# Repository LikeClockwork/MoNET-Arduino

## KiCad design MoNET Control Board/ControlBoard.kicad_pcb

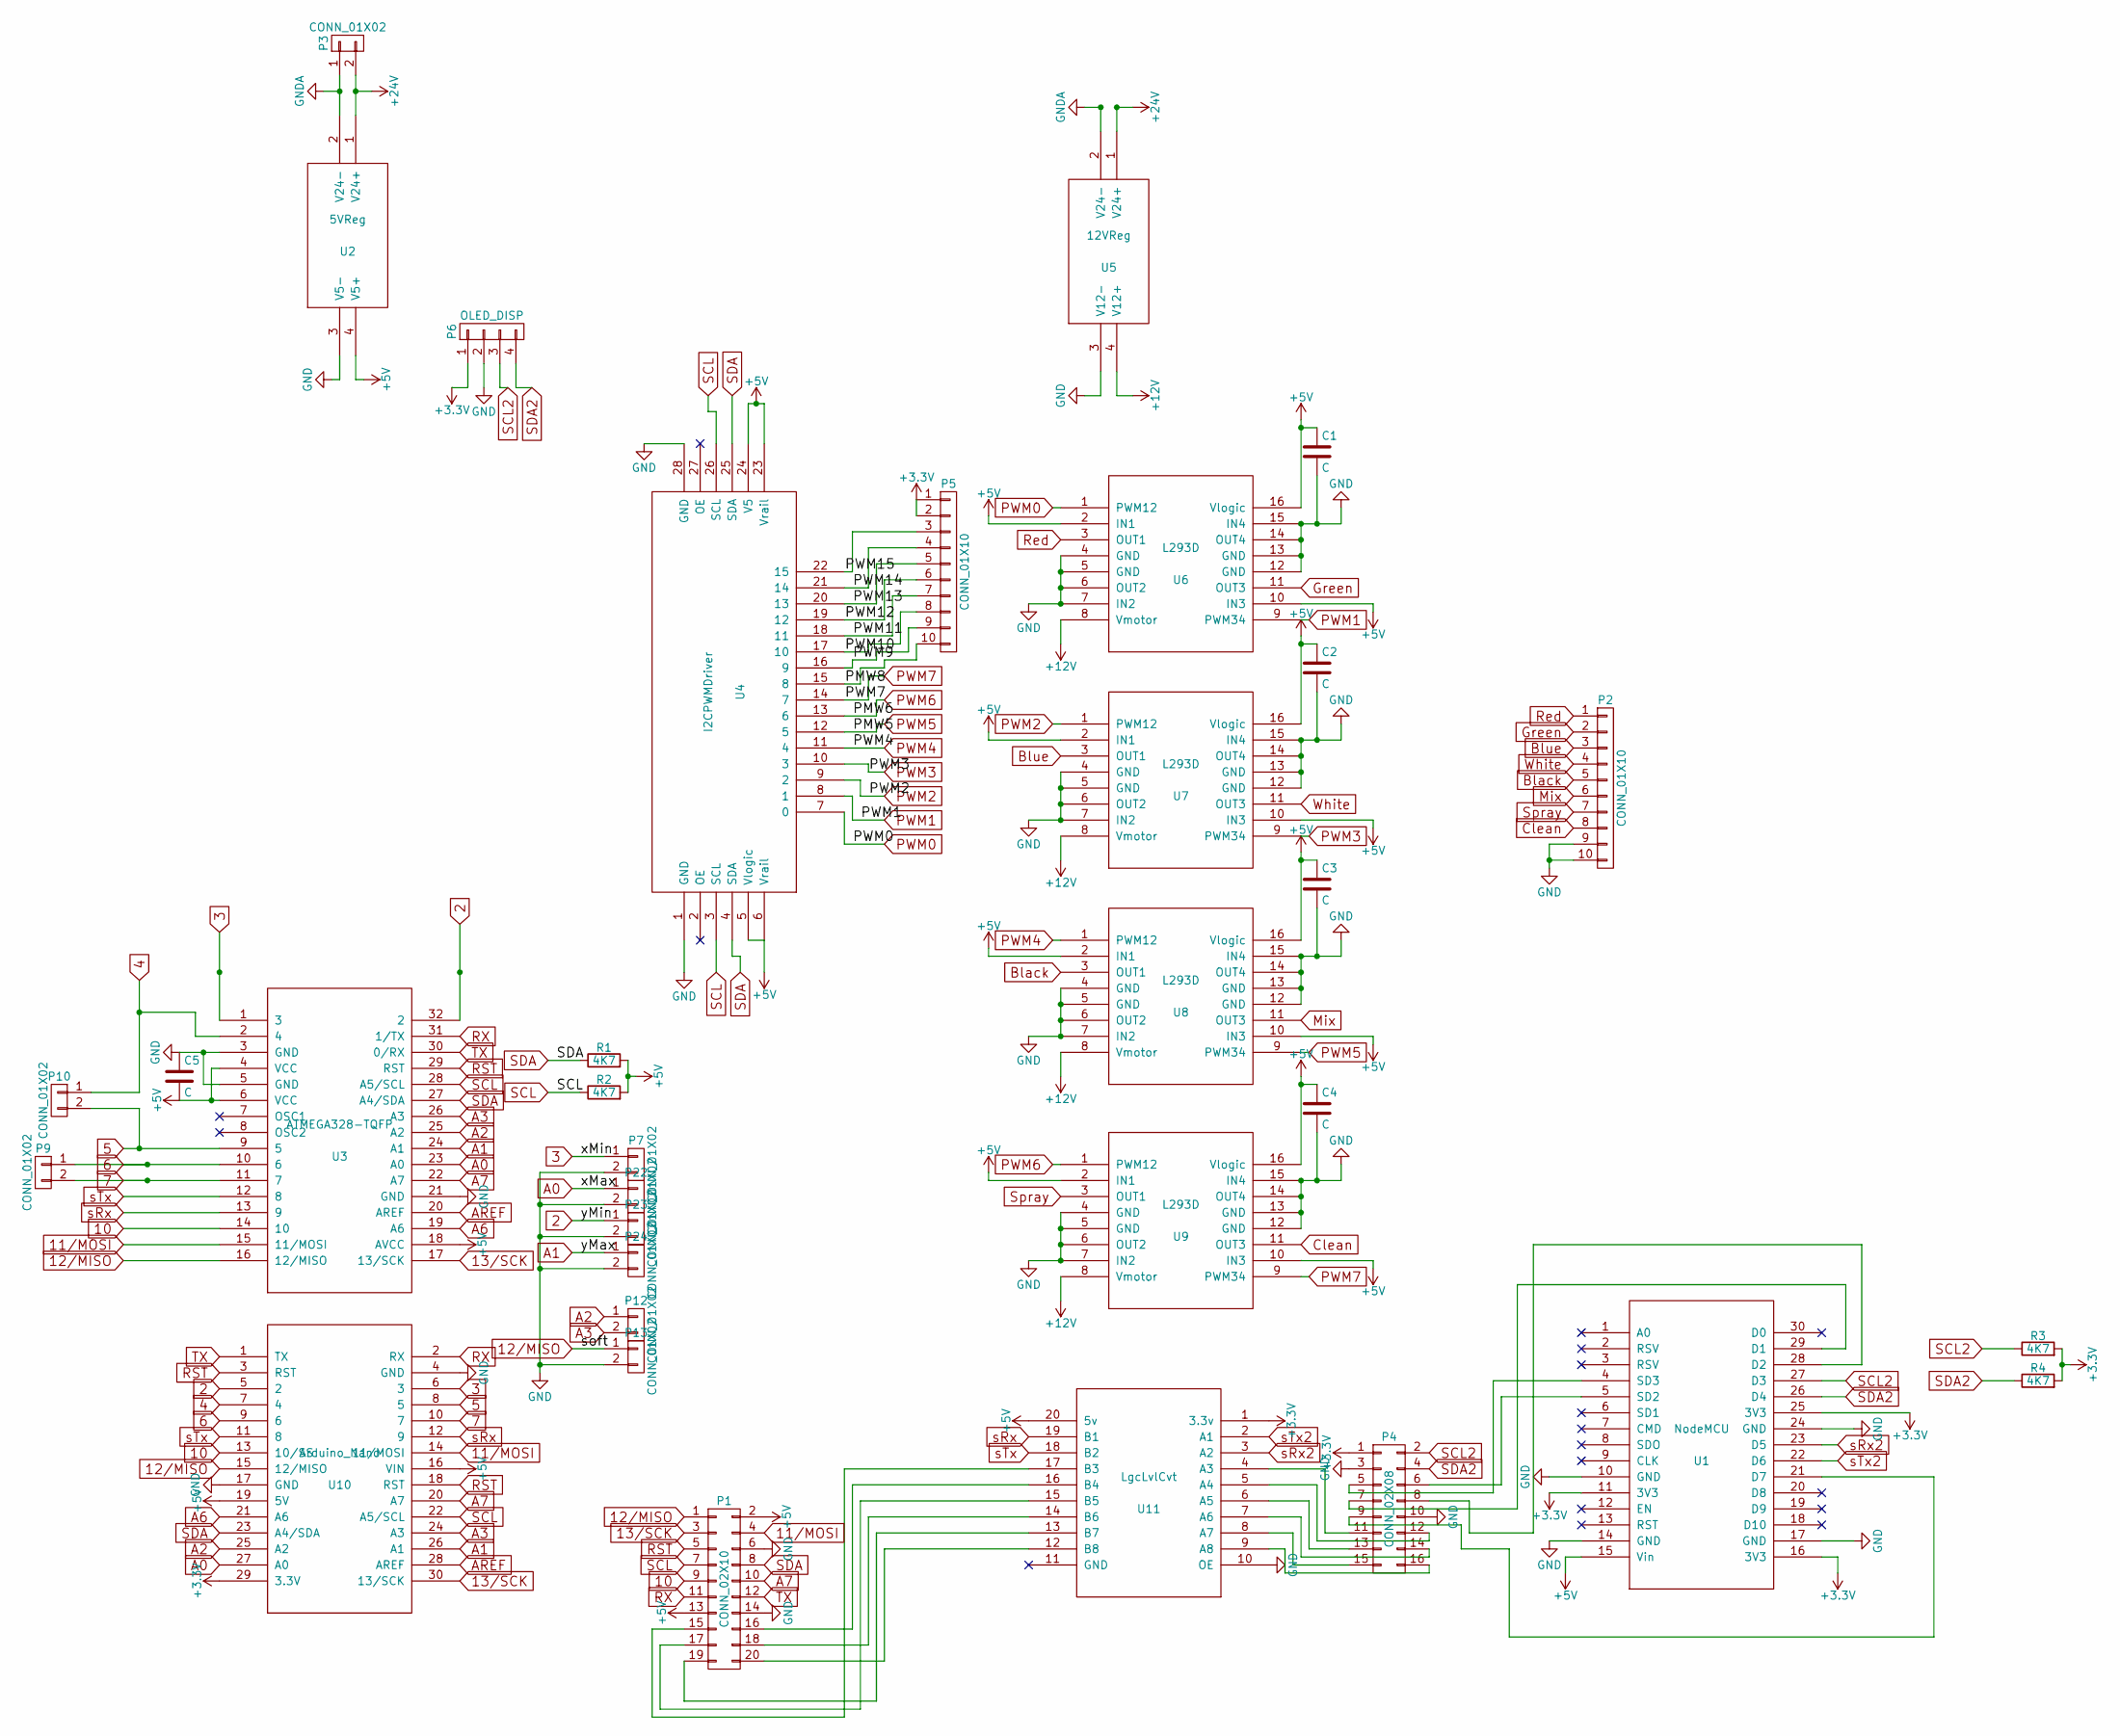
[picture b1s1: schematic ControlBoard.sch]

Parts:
C1, C2, C3, C4, C5: C; C_0603_HandSoldering
P1: CONN_02X10; Pin_Header_Straight_2x10
P2: CONN_01X10; SCREWTERM_01X10
P3, P7, P9, P10, P12, P13, P22, P23, P24: CONN_01X02; SCREWTERM_01X02
P4: CONN_02X08; Pin_Header_Straight_2x08
P5: CONN_01X10; Pin_Header_Straight_2x05
P6: OLED_DISP; Pin_Header_Straight_1x04
R1, R2, R3, R4: 4K7; R_0603_HandSoldering
U1: NodeMCU; NODEMCU
U2: 5VReg; RioRandVoltReg
U3: ATMEGA328-TQFP; TQFP32-08
U4: I2CPWMDriver; I2C_PWM_DRIVER
U5: 12VReg; RioRandVoltReg
U6, U7, U8, U9: L293D
U10: Arduino_Nano
U11: LgcLvlCvt

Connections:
2: P23.1, U3.32 (2), U10.5 (2)
3: P7.1, U3.1 (3), U10.6 (3)
4: P10.1, U3.2 (4), U10.7 (4)
5: P10.2, U3.9 (5), U10.8 (5)
6: P9.1, U3.10 (6), U10.9 (6)
7: P9.2, U3.11 (7), U10.10 (7)
10: P1.9, U3.14 (10), U10.13 (10/SS)
11/MOSI: P1.4, U3.15 (11/MOSI), U10.14 (11/MOSI)
12/MISO: P1.1, P13.1, U3.16 (12/MISO), U10.15 (12/MISO)
13/SCK: P1.3, U3.17 (13/SCK), U10.30 (13/SCK)
+3V3: P4.1, P5.1, P5.2, P6.1, R3.2, R4.2, U1.11 (3V3), U1.16 (3V3), U1.25 (3V3), U10.29 (3.3V), U11.1 (3.3v)
+5V: C1.1, C2.1, C3.1, C4.1, C5.2, P1.2, P1.13, R1.2, R2.2, U1.15 (Vin), U2.4 (V5+), U3.4 (VCC), U3.6 (VCC), U3.18 (AVCC), U4.5 (Vlogic), U4.6 (Vrail), U4.23 (Vrail), U4.24 (V5), U6.2 (IN1), U6.10 (IN3), U6.16 (Vlogic), U7.2 (IN1), U7.10 (IN3), U7.16 (Vlogic), U8.2 (IN1), U8.10 (IN3), U8.16 (Vlogic), U9.2 (IN1), U9.10 (IN3), U9.16 (Vlogic), U10.16 (VIN), U10.19 (5V), U11.20 (5v)
+12V: U5.4 (V12+), U6.8 (Vmotor), U7.8 (Vmotor), U8.8 (Vmotor), U9.8 (Vmotor)
+24V: P3.2, U2.1 (V24+), U5.1 (V24+)
/PMW8: P5.10, U4.15 (8)
/PWM9: P5.9, U4.16 (9)
/PWM10: P5.8, U4.17 (10)
/PWM11: P5.7, U4.18 (11)
/PWM12: P5.6, U4.19 (12)
/PWM13: P5.5, U4.20 (13)
/PWM14: P5.4, U4.21 (14)
/PWM15: P5.3, U4.22 (15)
A0: P22.1, U3.23 (A0), U10.27 (A0)
A1: P24.1, U3.24 (A1), U10.26 (A1)
A2: P12.1, U3.25 (A2), U10.25 (A2)
A3: P12.2, U3.26 (A3), U10.24 (A3)
A6: U3.19 (A6), U10.21 (A6)
A7: P1.10, U3.22 (A7), U10.20 (A7)
AREF: U3.20 (AREF), U10.28 (AREF)
Black: P2.5, U8.3 (OUT1)
Blue: P2.3, U7.3 (OUT1)
Clean: P2.8, U9.11 (OUT3)
GND: C1.2, C2.2, C3.2, C4.2, C5.1, P1.6, P1.14, P2.9, P2.10, P4.3, P4.10, P6.2, P7.2, P13.2, P22.2, P23.2, P24.2, U1.10 (GND), U1.14 (GND), U1.17 (GND), U1.24 (GND), U2.3 (V5-), U3.3 (GND), U3.5 (GND), U3.21 (GND), U4.1 (GND), U4.28 (GND), U5.3 (V12-), U6.4 (GND), U6.5 (GND), U6.6 (OUT2), U6.7 (IN2), U6.12 (GND), U6.13 (GND), U6.14 (OUT4), U6.15 (IN4), U7.4 (GND), U7.5 (GND), U7.6 (OUT2), U7.7 (IN2), U7.12 (GND), U7.13 (GND), U7.14 (OUT4), U7.15 (IN4), U8.4 (GND), U8.5 (GND), U8.6 (OUT2), U8.7 (IN2), U8.12 (GND), U8.13 (GND), U8.14 (OUT4), U8.15 (IN4), U9.4 (GND), U9.5 (GND), U9.6 (OUT2), U9.7 (IN2), U9.12 (GND), U9.13 (GND), U9.14 (OUT4), U9.15 (IN4), U10.4 (GND), U10.17 (GND), U11.10 (OE)
GNDA: P3.1, U2.2 (V24-), U5.2 (V24-)
Green: P2.2, U6.11 (OUT3)
Mix: P2.6, U8.11 (OUT3)
unnamed: P1.15, U11.17 (B3)
unnamed: P1.16, U11.16 (B4)
unnamed: P1.17, U11.15 (B5)
unnamed: P1.18, U11.14 (B6)
unnamed: P1.19, U11.13 (B7)
unnamed: P1.20, U11.12 (B8)
unnamed: P4.5, U1.4 (SD3)
unnamed: P4.6, U1.5 (SD2)
unnamed: P4.7, U1.29 (D1)
unnamed: P4.8, U1.28 (D2)
unnamed: P4.9, U1.21 (D7)
unnamed: P4.11, U11.4 (A3)
unnamed: P4.12, U11.5 (A4)
unnamed: P4.13, U11.6 (A5)
unnamed: P4.14, U11.7 (A6)
unnamed: P4.15, U11.8 (A7)
unnamed: P4.16, U11.9 (A8)
PWM0: U4.7 (0), U6.1 (PWM12)
PWM1: U4.8 (1), U6.9 (PWM34)
PWM2: U4.9 (2), U7.1 (PWM12)
PWM3: U4.10 (3), U7.9 (PWM34)
PWM4: U4.11 (4), U8.1 (PWM12)
PWM5: U4.12 (5), U8.9 (PWM34)
PWM6: U4.13 (6), U9.1 (PWM12)
PWM7: U4.14 (7), U9.9 (PWM34)
RST: P1.5, U3.29 (RST), U10.3 (RST), U10.18 (RST)
RX: P1.11, U3.31 (1/TX), U10.2 (RX)
Red: P2.1, U6.3 (OUT1)
SCL: P1.7, R2.1, U3.28 (A5/SCL), U4.3 (SCL), U4.26 (SCL), U10.22 (A5/SCL)
SCL2: P4.2, P6.3, R3.1, U1.27 (D3)
SDA: P1.8, R1.1, U3.27 (A4/SDA), U4.4 (SDA), U4.25 (SDA), U10.23 (A4/SDA)
SDA2: P4.4, P6.4, R4.1, U1.26 (D4)
Spray: P2.7, U9.3 (OUT1)
TX: P1.12, U3.30 (0/RX), U10.1 (TX)
White: P2.4, U7.11 (OUT3)
sRx: U3.13 (9), U10.12 (9), U11.19 (B1)
sRx2: U1.23 (D5), U11.3 (A2)
sTx: U3.12 (8), U10.11 (8), U11.18 (B2)
sTx2: U1.22 (D6), U11.2 (A1)

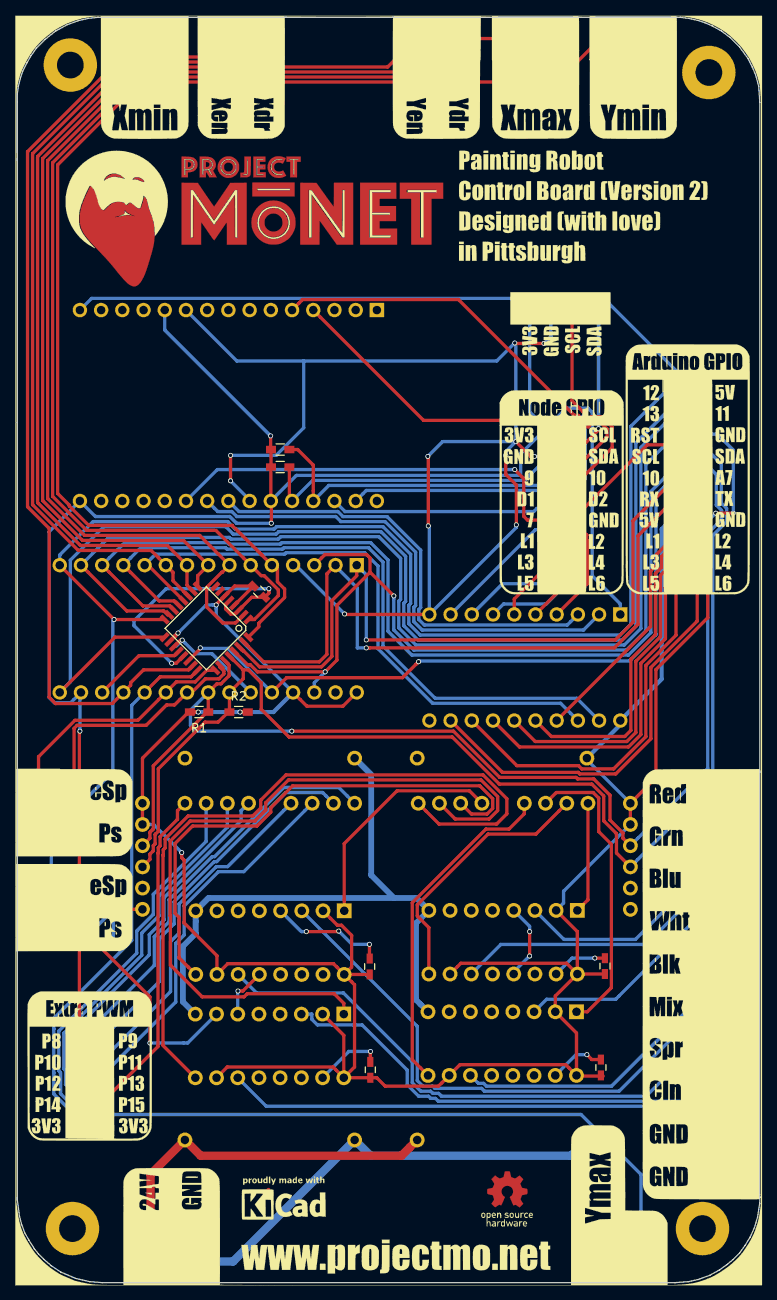
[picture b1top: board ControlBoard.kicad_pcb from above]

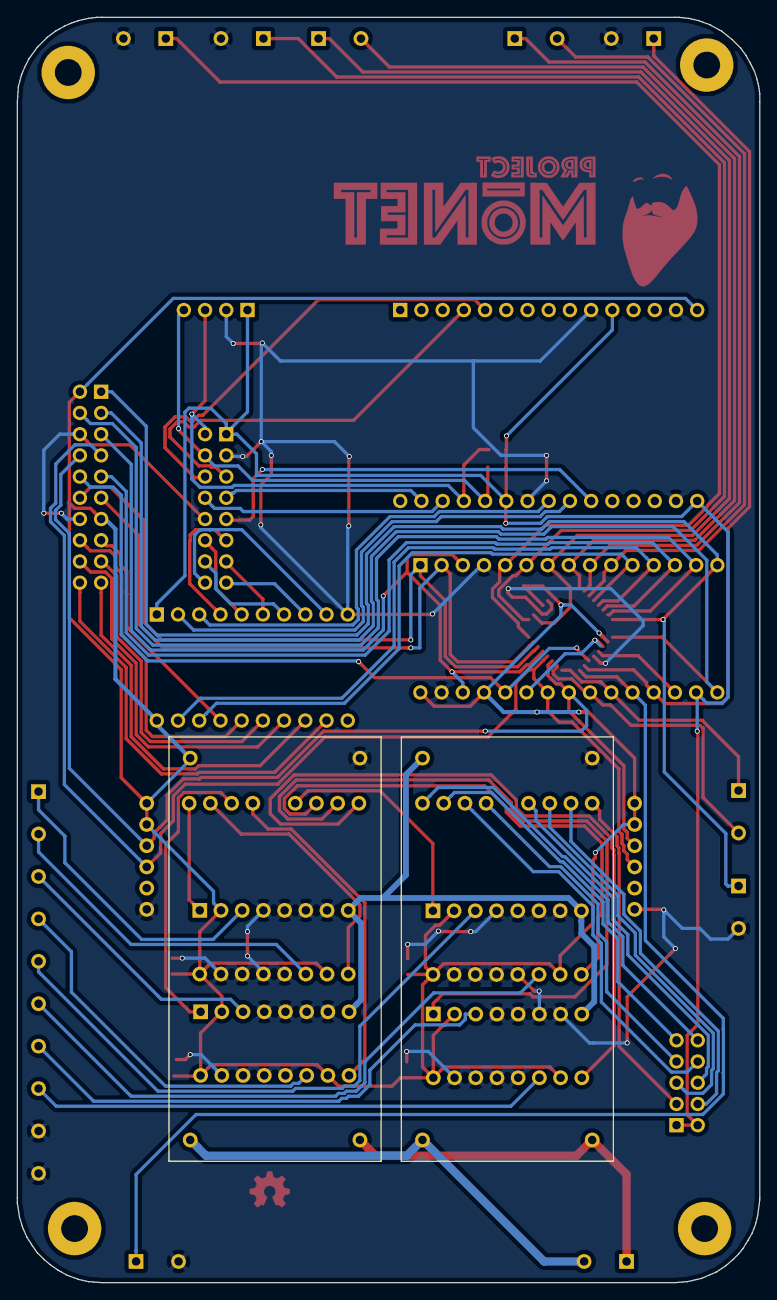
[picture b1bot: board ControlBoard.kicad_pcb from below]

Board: 2 copper layers, 88.9 x 151.5 mm, 34 parts (2 on the bottom side), 75 nets.

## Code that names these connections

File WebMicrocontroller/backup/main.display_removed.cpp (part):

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      red = 0,    //amount to run paint motors
      green = 0,
      blue = 0,
      white = 0,
      black = 0,
      mix = 0,
      dispense = 0,
      clean = 0,
      speed = 0;  //speed to move at to destination
    unsigned int errorCount;
      String JSON;
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
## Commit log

2016-12-31 Added DXF
